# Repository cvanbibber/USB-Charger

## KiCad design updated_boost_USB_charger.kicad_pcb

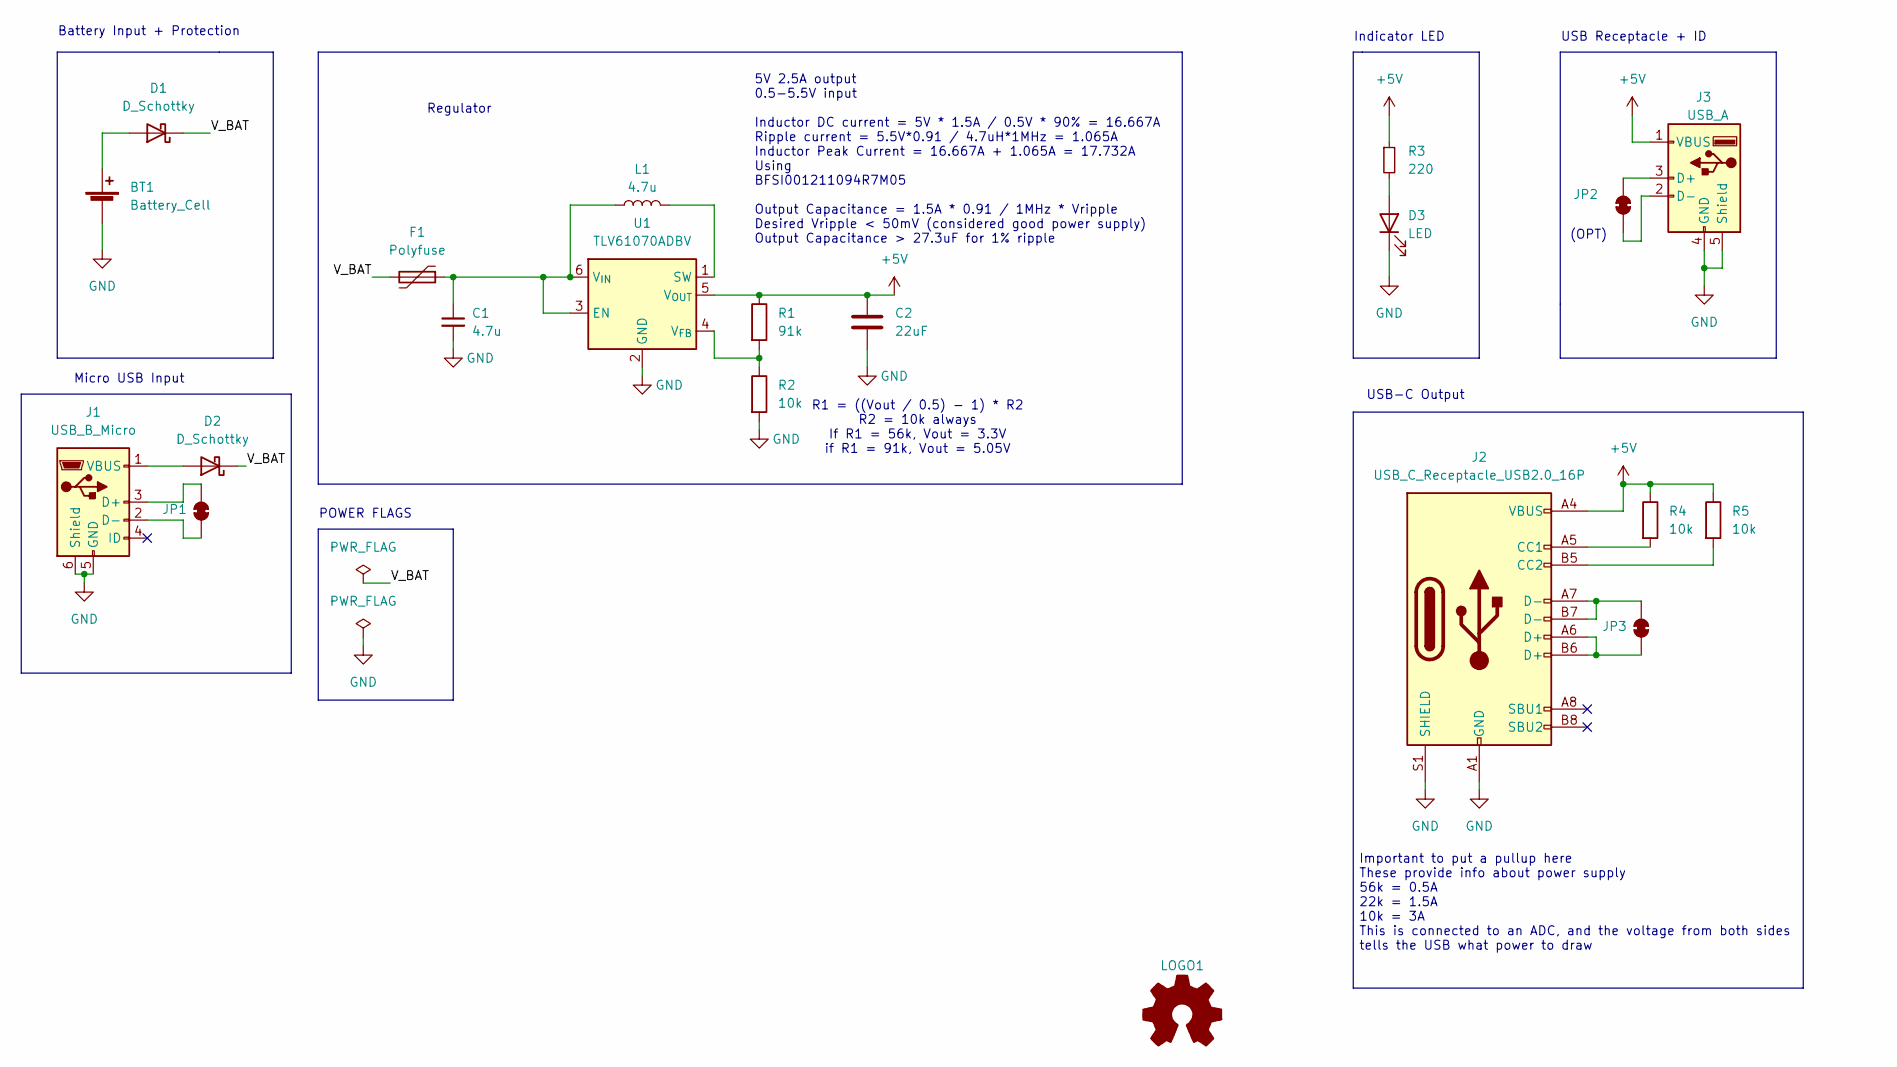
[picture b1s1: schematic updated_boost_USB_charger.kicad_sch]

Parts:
BT1: Battery_Cell; PinHeader_1x02_P2.54mm_Vertical; Digikey A128003CT-ND
C1: 4.7u; C_0805_2012Metric_Pad1.18x1.45mm_HandSolder; Digikey 478-0805YC106KAT2ADKR-ND
C2: 22uF; C_0603_1608Metric_Pad1.08x0.95mm_HandSolder
D1, D2: D_Schottky; D_SMA_Handsoldering
D3: LED; LED_0805_2012Metric_Pad1.15x1.40mm_HandSolder; Digikey 475-1410-6-ND
F1: Polyfuse; Fuse_1206_3216Metric_Pad1.42x1.75mm_HandSolder; Digikey 18-1812L260/16MR-ADKR-ND
J1: USB_B_Micro; CONN_10118192-0002LF_AMP
J2: USB_C_Receptacle_USB2.0_16P; USB_C_Receptacle_GCT_USB4105-xx-A_16P_TopMnt_Horizontal
J3: USB_A; USB_A_Molex_67643_Horizontal; Digikey 380-1412-ND
JP1, JP2, JP3: SolderJumper_2_Bridged; SolderJumper-2_P1.3mm_Bridged_RoundedPad1.0x1.5mm
L1: 4.7u; TMPA 1005SV-4R7MN-D
LOGO1: Logo_Open_Hardware_Small; ieee
R1: 91k; R_0603_1608Metric_Pad0.98x0.95mm_HandSolder
R2, R4, R5: 10k; R_0805_2012Metric_Pad1.20x1.40mm_HandSolder
R3: 220; R_0603_1608Metric_Pad0.98x0.95mm_HandSolder; Digikey 749-1629-6-ND
U1: TLV61070ADBV; SOT-23-6

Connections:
+5V: C2.1, J2.A4 (VBUS), J2.A9 (VBUS), J2.B4 (VBUS), J2.B9 (VBUS), J3.1 (VBUS), R1.1, R3.1, R4.1, R5.1, U1.5 (V_{OUT})
/V_BAT: D1.1 (K), D2.1 (K), F1.2
GND: BT1.2 (-), C1.2, C2.2, D3.1 (K), J1.5 (GND), J1.6 (Shield), J2.A1 (GND), J2.A12 (GND), J2.B1 (GND), J2.B12 (GND), J2.S1 (SHIELD), J3.4 (GND), J3.5 (Shield), R2.2, U1.2 (GND)
unnamed: BT1.1 (+), D1.2 (A)
unnamed: D2.2 (A), J1.1 (VBUS)
unnamed: D3.2 (A), R3.2
unnamed: J1.3 (D+), JP1.2 (B)
unnamed: J1.2 (D-), JP1.1 (A)
unnamed: J2.A5 (CC1), R4.2
unnamed: J2.B5 (CC2), R5.2
unnamed: J3.3 (D+), JP2.2 (B)
unnamed: J3.2 (D-), JP2.1 (A)
unnamed: J2.A6 (D+), J2.B6 (D+), JP3.1 (A)
unnamed: J2.A7 (D-), J2.B7 (D-), JP3.2 (B)
unnamed: C1.1, F1.1, L1.1, U1.3 (EN), U1.6 (V_{IN})
unnamed: L1.2, U1.1 (SW)
unnamed: R1.2, R2.1, U1.4 (V_{FB})

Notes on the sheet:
POWER FLAGS
Indicator LED
USB Receptacle + ID
Important to put a pullup here These provide info about power supply 56k = 0.5A 22k = 1.5A 10k = 3A This is connected to an ADC, and the voltage from both sides tells the USB what power to draw
Regulator
5V 2.5A output 0.5-5.5V input Inductor DC current = 5V * 1.5A / 0.5V * 90% = 16.667A Ripple current = 5.5V*0.91 / 4.7uH*1MHz = 1.065A Inductor Peak Current = 16.667A + 1.065A = 17.732A Using BFSI001211094R7M05 Output Capacitance = 1.5A * 0.91 / 1MHz * Vripple Desired Vripple < 50mV (considered good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
USB-C Output
Micro USB Input
(OPT)
R1 = ((Vout / 0.5) - 1) * R2 R2 = 10k always If R1 = 56k, Vout = 3.3V if R1 = 91k, Vout = 5.05V
Battery Input + Protection

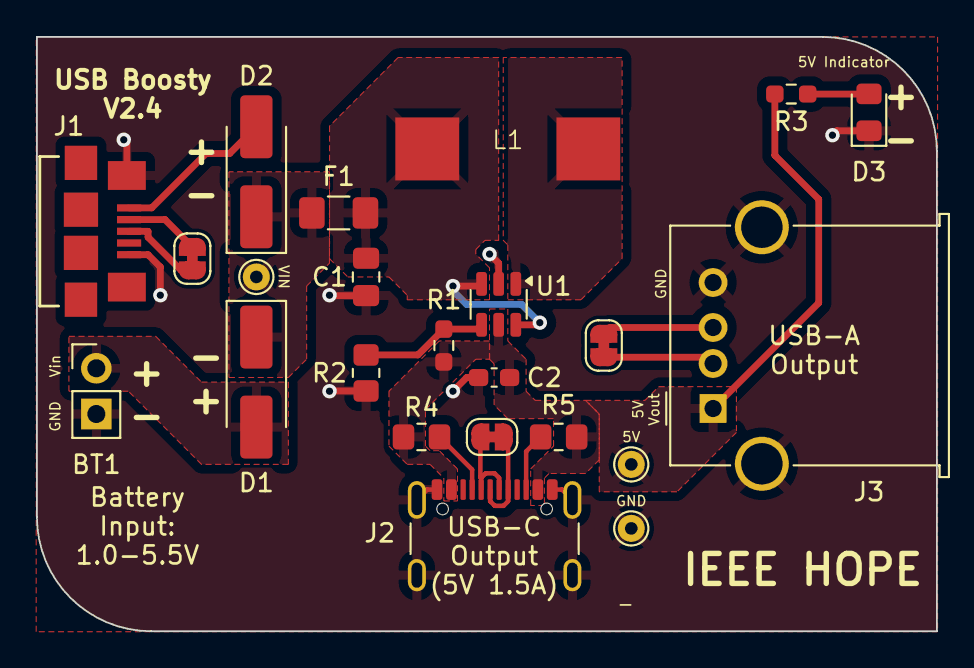
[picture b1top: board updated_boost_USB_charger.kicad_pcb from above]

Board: 2 copper layers, 50.0 x 33.0 mm, 21 parts (1 on the bottom side), 17 nets.

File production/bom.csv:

Designator,Footprint,Quantity,Value,LCSC Part #
BT1,PinHeader_1x02_P2.54mm_Vertical,1,Battery_Cell,
C1,0805,1,4.7u,
C2,0603,1,22uF,
"D1, D2",D_SMA_Handsoldering,2,D_Schottky,
D3,0805,1,LED,
F1,1206,1,Polyfuse,
J1,CONN_10118192-0002LF_AMP,1,USB_B_Micro,
J2,USB_C_Receptacle_GCT_USB4105-xx-A_16P_TopMnt_Horizontal,1,USB_C_Receptacle_USB2.0_16P,
J3,USB_A_Molex_67643_Horizontal,1,USB_A,
L1,TMPA 1005SV-4R7MN-D,1,4.7u,
LOGO1,ieee,1,Logo_Open_Hardware_Small,
R1,0603,1,91k,
"R2, R4, R5",0805,3,10k,
R3,0603,1,220,
U1,SOT-23-6,1,TLV61070ADBV,

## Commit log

2025-02-17 pushed all data
